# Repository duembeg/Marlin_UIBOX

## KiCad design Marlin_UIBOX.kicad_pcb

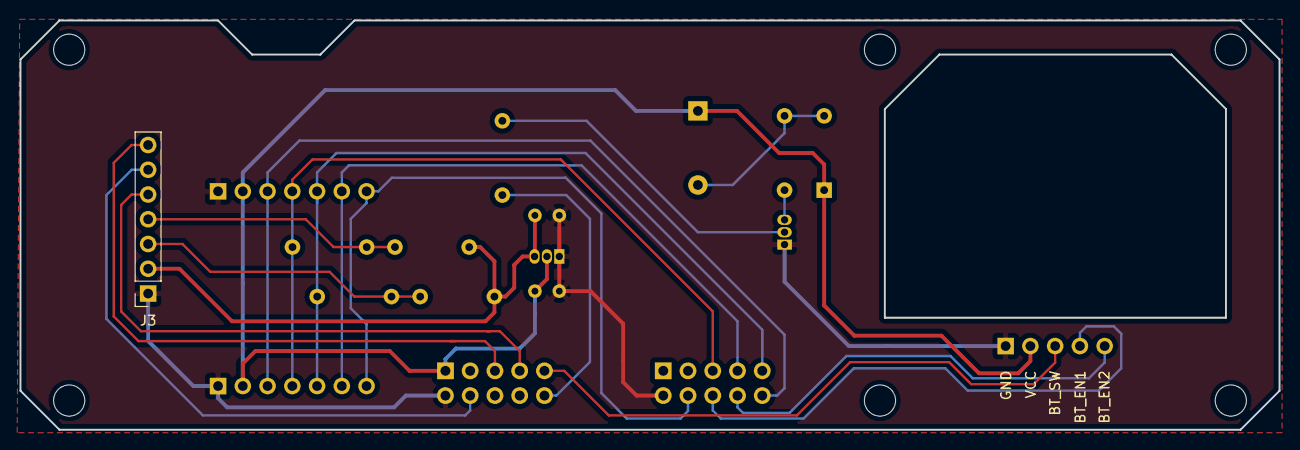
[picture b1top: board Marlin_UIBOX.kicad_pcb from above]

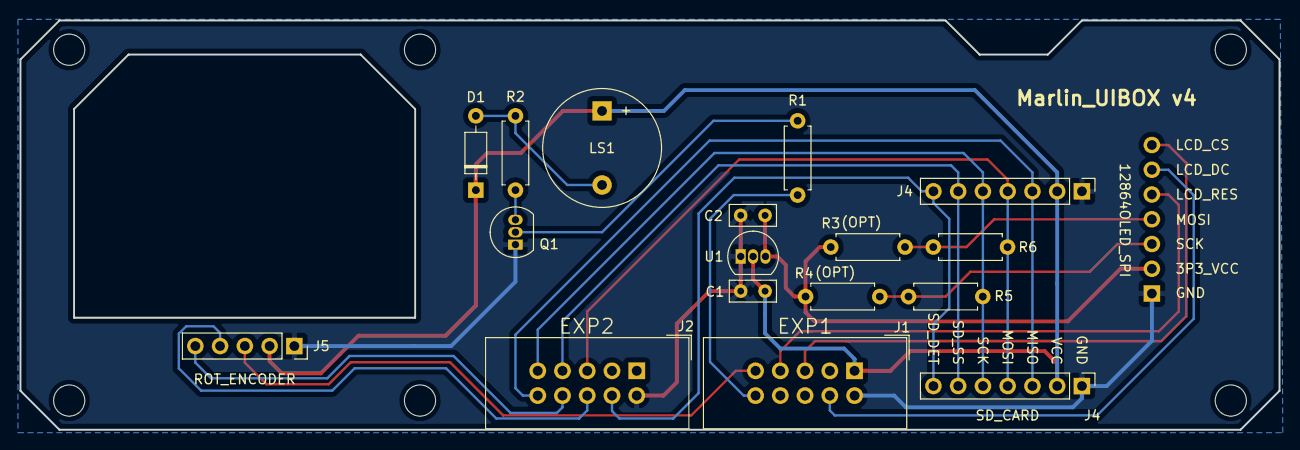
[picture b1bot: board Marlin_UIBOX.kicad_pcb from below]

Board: 2 copper layers, 129.2 x 42.0 mm, 18 parts (17 on the bottom side), 20 nets.

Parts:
C1, C2: 1uf; C_Rect_L4.6mm_W2.0mm_P2.50mm_MKS02_FKP02
D1: D; D_DO-35_SOD27_P7.62mm_Horizontal
J1: EXP1; IDC-Header_2x05_P2.54mm_Vertical
J2: EXP2; IDC-Header_2x05_P2.54mm_Vertical
J3: 12864OLED_SPI; PinSocket_1x07_P2.54mm_Vertical
J4, J4#2: SD_CARD; Pin_Header_Straight_1x07_Pitch2.54mm
J5: ROT_ENCODER; PinSocket_1x05_P2.54mm_Vertical
LS1: Speaker; Buzzer_12x9.5RM7.6
Q1: 2N3904; TO-92_Inline
R1, R5, R6: 1K; R_Axial_DIN0207_L6.3mm_D2.5mm_P7.62mm_Horizontal
R2: 100; R_Axial_DIN0207_L6.3mm_D2.5mm_P7.62mm_Horizontal
R3, R4: 2.2K; R_Axial_DIN0207_L6.3mm_D2.5mm_P7.62mm_Horizontal
U1: MCP1700-3302E_TO92; TO-92_Inline

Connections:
/3P3_VCC: C2.1, J3.2, R3.1, R4.1, U1.3
/BEEPER: J1.10, R1.1
/BT_EN1: J2.6, J5.4
/BT_EN2: J2.8, J5.5
/BT_SW: J1.9, J5.3
/LCD_CS: J1.5, J3.7
/LCD_DC: J1.4, J3.6
/LCD_MOSI: J3.4, R3.2, R6.2
/LCD_RES: J1.7, J3.5
/LCD_SCK: J3.3, R4.2, R5.2
/MISO: J2.10, J4.3, J4#2.3
/MOSI: J2.5, J4.4, J4#2.4, R6.1
/SCK: J2.9, J4.5, J4#2.5, R5.1
/SD_DET: J2.4, J4.7, J4#2.7
/SD_SS: J2.7, J4.6, J4#2.6
GND: C1.2, C2.2, J1.2, J2.2, J3.1, J4.1, J4#2.1, J5.1, Q1.1, U1.1
unnamed: D1.2, LS1.2, R2.1
unnamed: Q1.2, R1.2
unnamed: Q1.3, R2.2
VCC: C1.1, D1.1, J1.1, J4.2, J4#2.2, J5.2, LS1.1, U1.2

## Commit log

2018-12-30 Initial checkin
2019-01-16 PCB ver2 full board to board connections
    * Complete re-do PCB to have PCB to PCB connectors no wire needed
    * Went with 2 layer PCB instead of trying to make single layer...
2019-01-16 Move parts to fit both Replicator 1 and 2
2019-01-16 More tweaking
    More tweaking
2020-02-14 This is the v1 that was fabricated by board house
2020-02-14 Added CAD files
2020-02-14 Added second header for second position on SD card pcb
2020-02-14 updated .ignore file
2020-02-19 Generated lates manufacturing files to send to board house...
2020-03-25 Added 3.3V Reg for LCD
    * Added 3.3V Reg for LCD
    * Added optional pull up resistors for LCD
    * Added series resistors fro SPI signal for LCD to help with over/under
    shoot
2020-03-25 Updated PCB legends/silk screen
